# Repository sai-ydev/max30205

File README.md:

# Max30205 Contact Thermometer

MAX30205 based contact thermometer using Seeduino's Xiao

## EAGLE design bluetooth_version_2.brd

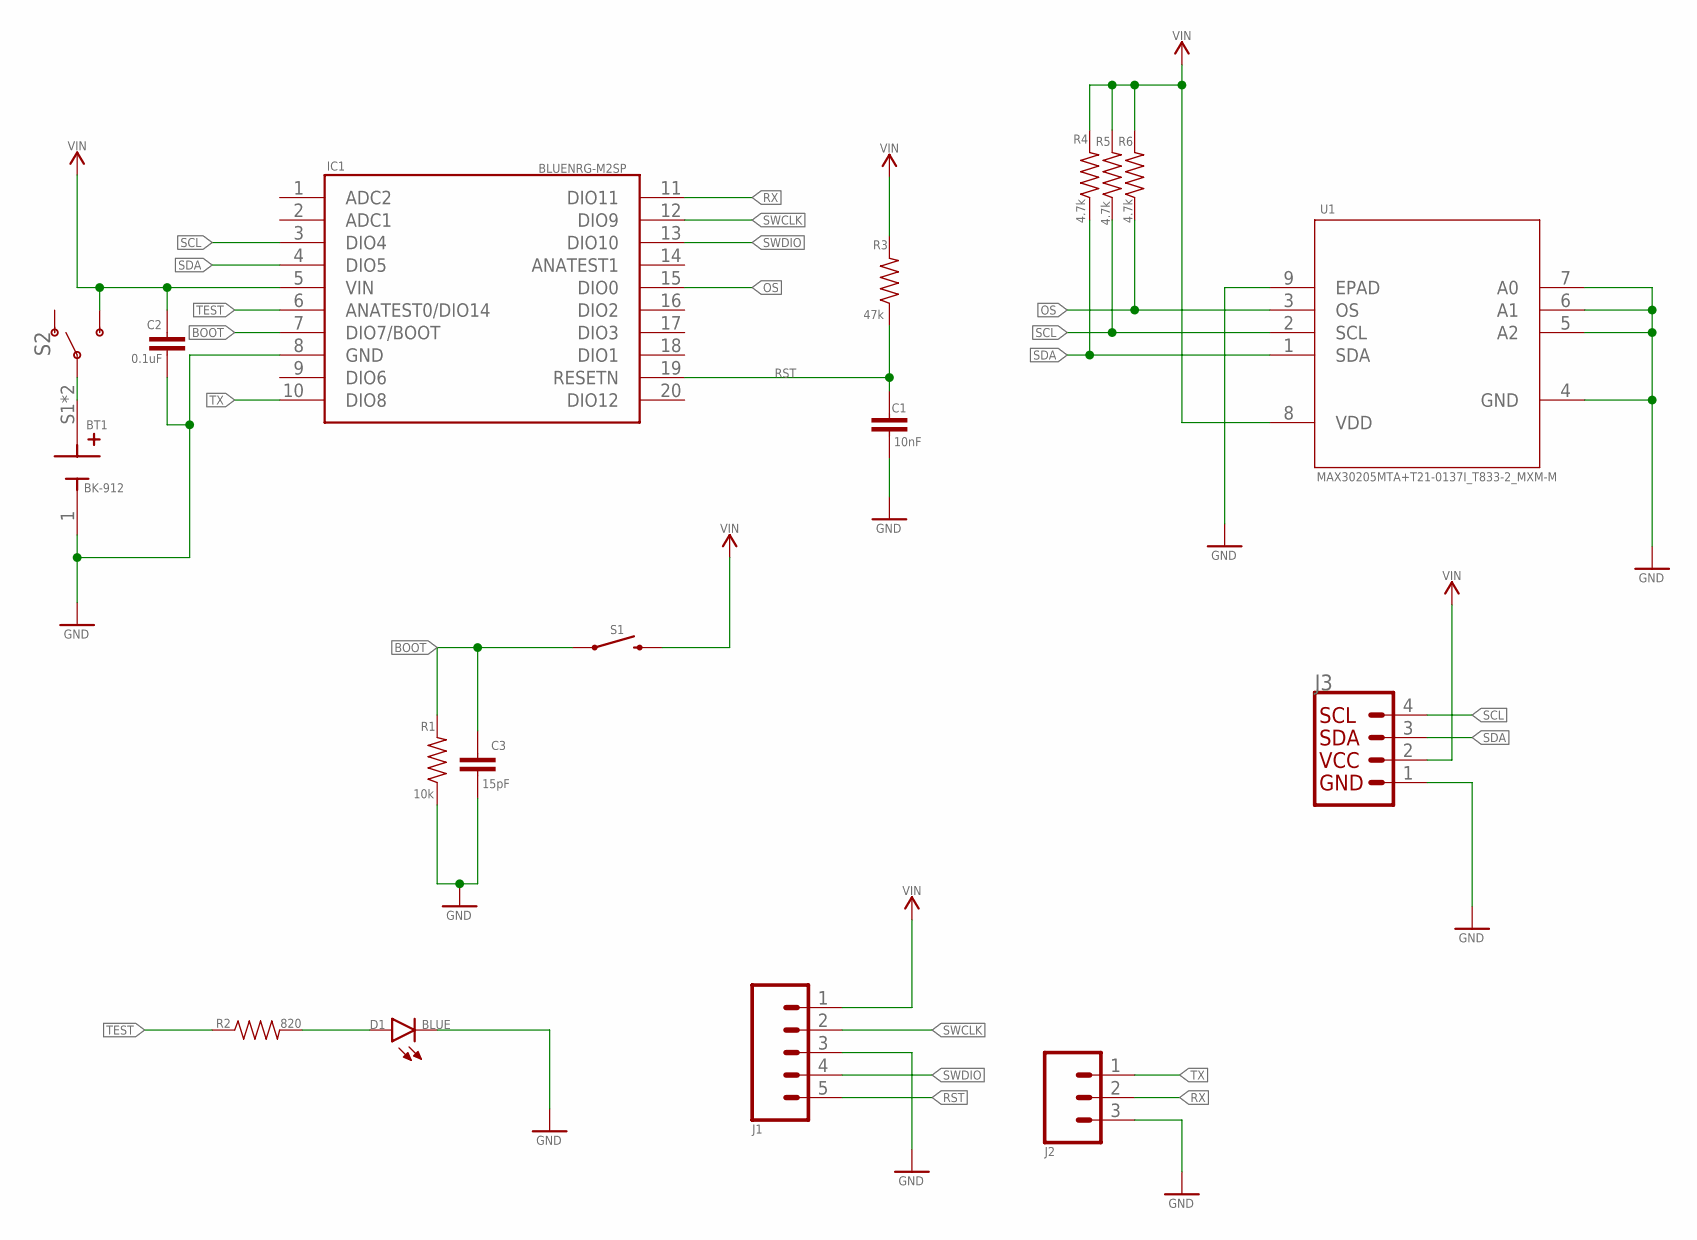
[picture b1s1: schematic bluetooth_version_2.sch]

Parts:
BT1: BK-912; BAT_BK-912
C1: 10nF; 0603
C2: 0.1uF; 0603
C3: 15pF; 0603
D1: BLUE; LED-0603
IC1: BLUENRG-M2SP; BLUENRGM2SP
J1: CONN_05; 1X05
J2: 455-1750-1-ND; 1X03
J3: I2C_STANDARD; 1X04
R1: 10k; 0603
R2: 820; 0603
R3: 47k; 0603
R4, R5, R6: 4.7k; 0603
S1: MOMENTARY-SWITCH-SPST-SMD-4.6X2.8MM; TACTILE_SWITCH_SMD_4.6X2.8MM
S2: SWITCH-SPDT-SMD-RIGHT-ANGLE; SWITCH_SPST_SMD_A
U1: MAX30205MTA+T21-0137I_T833-2_MXM-M; 21-0137I_T833-2_MXM-M

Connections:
BOOT: C3.1, IC1.7 (DIO7/BOOT), R1.2, S1.1, S1.2 (1)
GND: BT1.1 (-), C1.2, C2.2, C3.2, D1.C, IC1.8 (GND), J1.3, J2.3, J3.1, R1.1, U1.4 (GND), U1.5 (A2), U1.6 (A1), U1.7 (A0), U1.9 (EPAD)
unnamed: D1.A, R2.2
unnamed: BT1.S1 (+), BT1.S2 (+), S2.2
OS: IC1.15 (DIO0), R6.1, U1.3 (OS)
RST: C1.1, IC1.19 (RESETN), J1.5, R3.1
RX: IC1.11 (DIO11), J2.2
SCL: IC1.3 (DIO4), J3.4, R5.1, U1.2 (SCL)
SDA: IC1.4 (DIO5), J3.3, R4.1, U1.1 (SDA)
SWCLK: IC1.12 (DIO9), J1.2
SWDIO: IC1.13 (DIO10), J1.4
TEST: IC1.6 (ANATEST0/DIO14), R2.1
TX: IC1.10 (DIO8), J2.1
VIN: C2.1, IC1.5 (VIN), J1.1, J3.2, R3.2, R4.2, R5.2, R6.2, S1.3 (2), S1.4 (2), S2.3 (S), U1.8 (VDD)

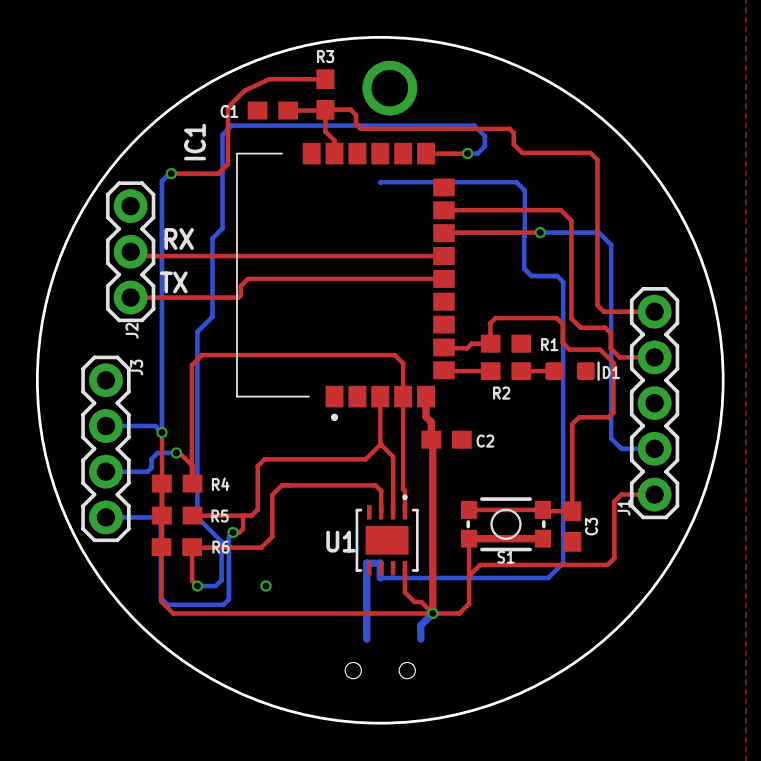
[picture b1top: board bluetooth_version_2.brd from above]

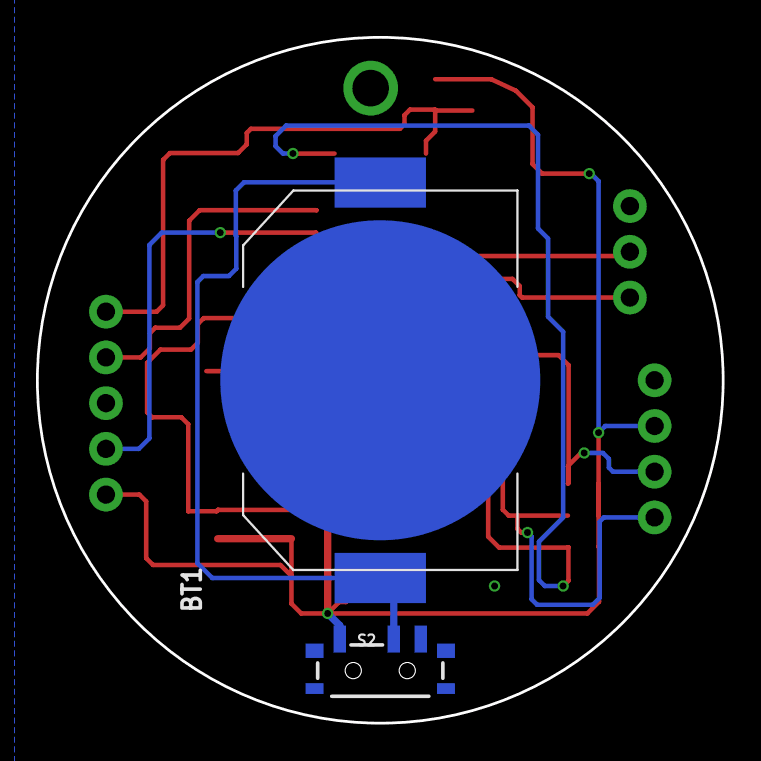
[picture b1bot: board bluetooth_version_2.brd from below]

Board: 2 copper layers, 38.1 x 38.1 mm, 18 parts (2 on the bottom side), 14 nets.

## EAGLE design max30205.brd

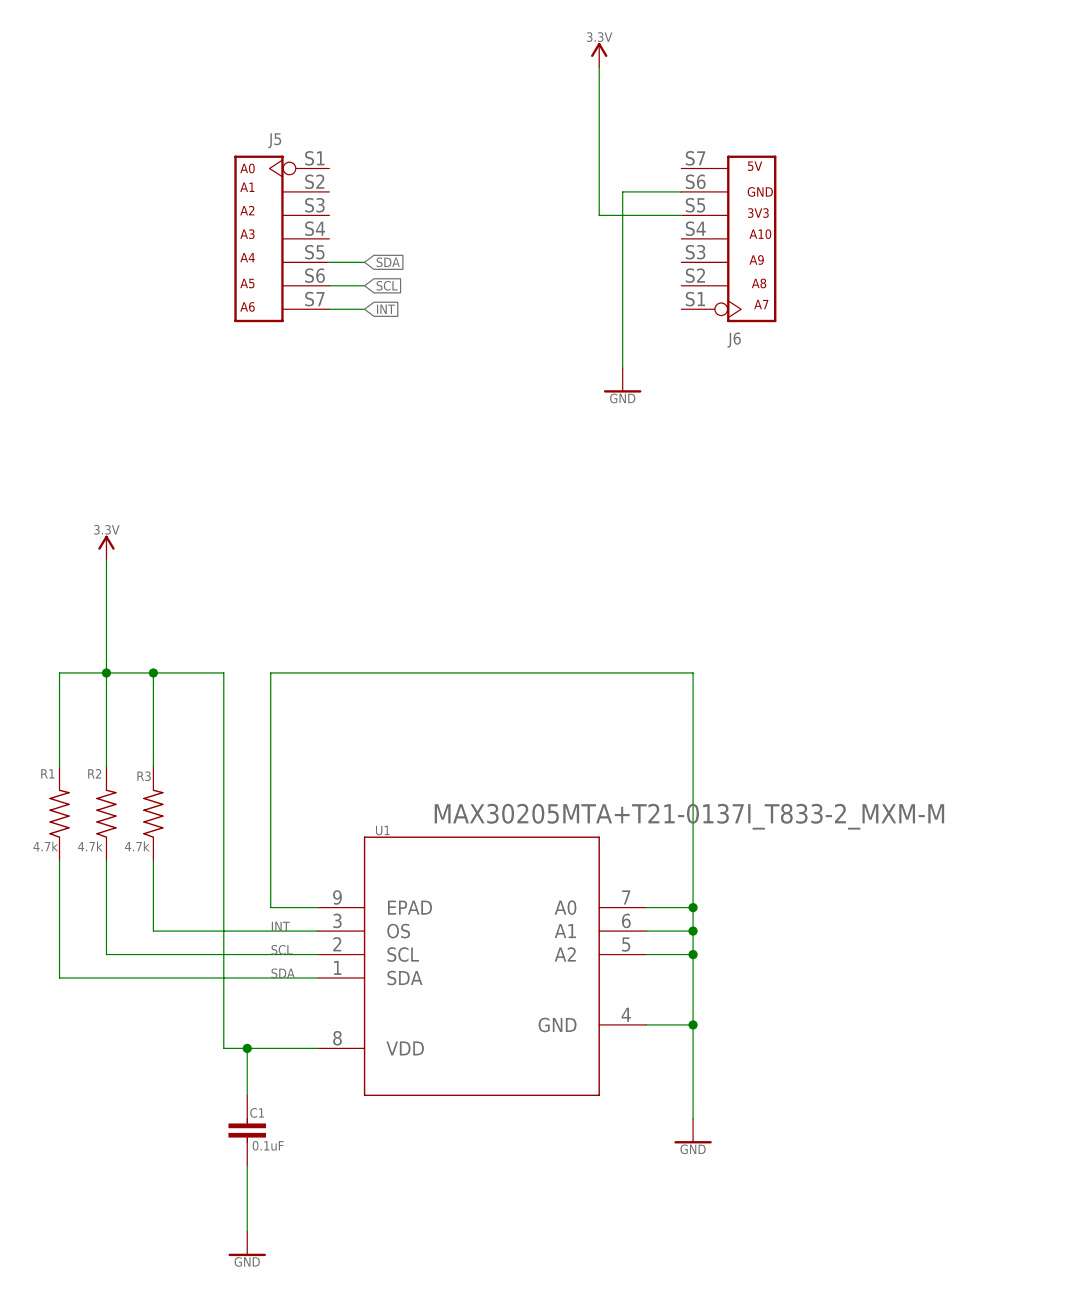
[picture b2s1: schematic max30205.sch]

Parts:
C1: 0.1uF; 0603
J5, J6: DNP; CONNECTOR-V2
R1, R2, R3: 4.7k; 0603
U1: MAX30205MTA+T21-0137I_T833-2_MXM-M; 21-0137I_T833-2_MXM-M

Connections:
3.3V: C1.1, J6.S5 (5), R1.2, R2.2, R3.2, U1.8 (VDD)
GND: C1.2, J6.S6 (6), U1.4 (GND), U1.5 (A2), U1.6 (A1), U1.7 (A0), U1.9 (EPAD)
INT: J5.S7 (7), R3.1, U1.3 (OS)
SCL: J5.S6 (6), R2.1, U1.2 (SCL)
SDA: J5.S5 (5), R1.1, U1.1 (SDA)

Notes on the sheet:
A10
3V3
GND

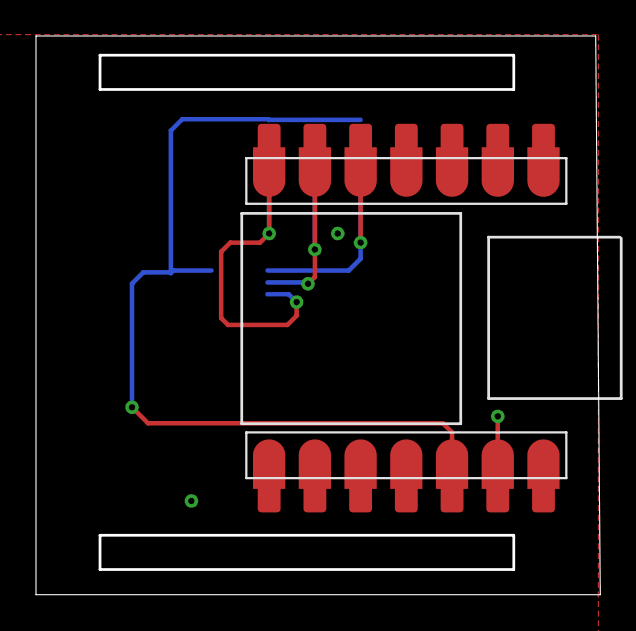
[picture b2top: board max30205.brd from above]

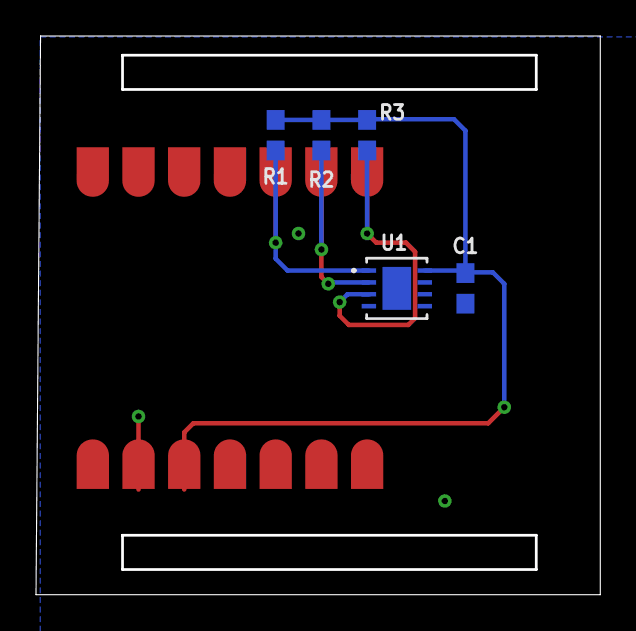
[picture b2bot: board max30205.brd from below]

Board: 2 copper layers, 31.3 x 31.0 mm, 7 parts (5 on the bottom side), 5 nets.

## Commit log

2020-07-06 Check-in
2020-07-20 Uploading images
2020-08-06 Check-in of BoM
2020-09-23 Bluetooth version check-in
2020-12-22 v2 check-in

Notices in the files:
parts and their libraries:
SparkFun-Capacitors: Licensing: Creative Commons ShareAlike 4.0 International - https://creativecommons.org/licenses/by-sa/4.0
COPYRIGHT: Copyright (C) 2018 Accelerated Designs. All rights reserved
